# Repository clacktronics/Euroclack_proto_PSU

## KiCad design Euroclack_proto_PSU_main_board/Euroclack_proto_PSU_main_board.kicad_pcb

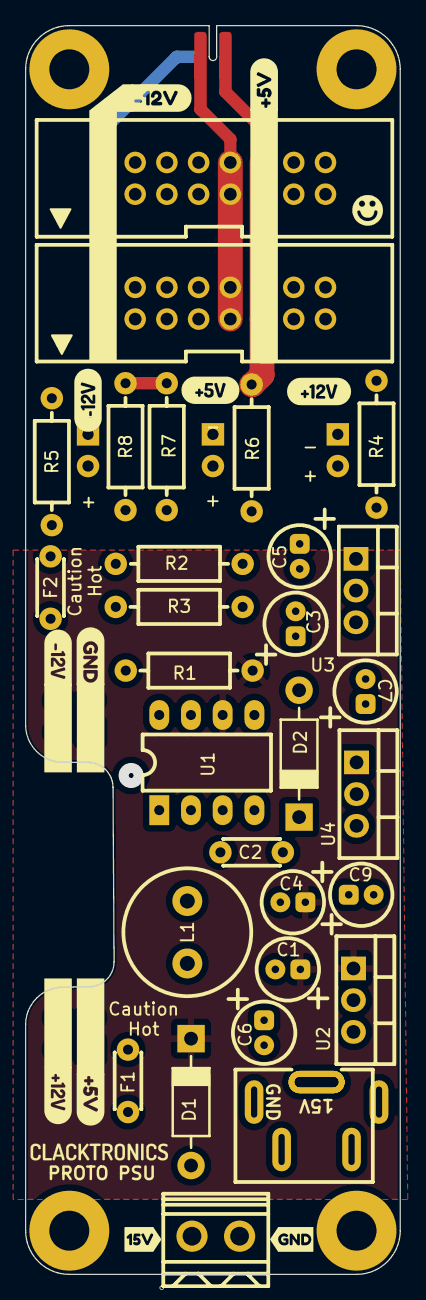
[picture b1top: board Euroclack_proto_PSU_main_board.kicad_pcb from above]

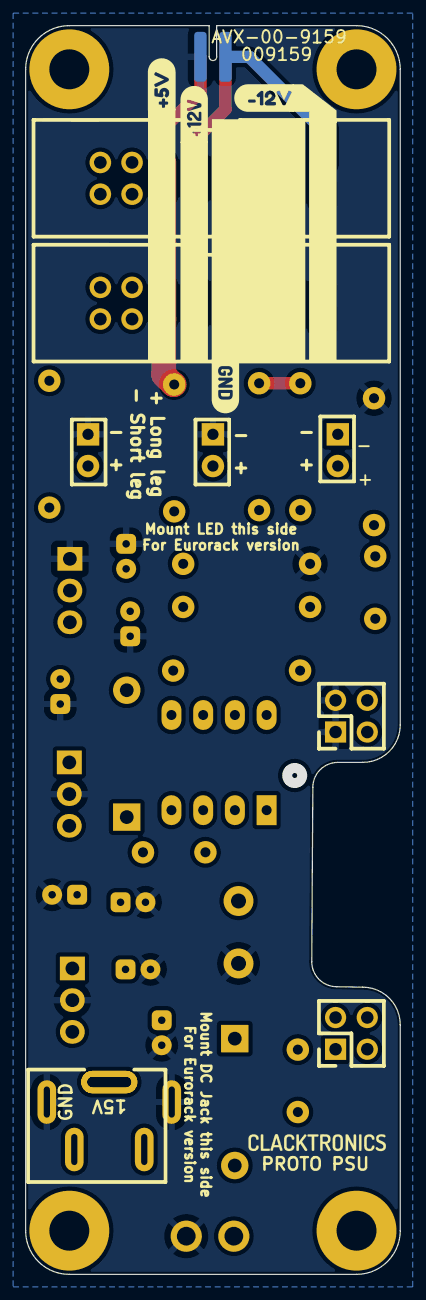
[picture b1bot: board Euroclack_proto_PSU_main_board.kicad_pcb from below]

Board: 4 copper layers, 30.0 x 100.0 mm, 51 parts (7 on the bottom side), 16 nets.

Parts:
C1, C3, C4, C5: 100uF; C_TH_Elec_5mm_P2mm
C2: 220p; C_TH_Disc_P5.00mm
C6, C7, C9: 10uf; C_TH_Elec_5mm_P2mm
D1, D2: 1N5819; D_TH_DO-41_P10.16mm
D3, D4, D5: LED; LED_D3.0mm
F1, F2: JK60-030; C_TH_Disc_P5.00mm
J1, J4: Jack-DC; DC-012A-20A
J2, J3: Conn_02x08_Odd_Even; Eurorack_16_header
J5: Screw_Terminal_01x02; CONN-TH_2P-P3.81_DB125-3.81-2P-BK-S
J6, J7: Conn_02x02_Odd_Even; PinHeader_2x02_P2.54mm_Vertical
J8: AVX-00-9159; AVX-00-9159-004
L1: 220uH; L_Radial_D10.0mm_P5.00mm_Neosid_SD12_style3
R1: 0R220; R_TH_Axial_250mw_P10.16mm_Horizontal
R2, R4, R5, R6, R7, R8: 11k; R_TH_Axial_250mw_P10.16mm_Horizontal
R3: 1k; R_TH_Axial_250mw_P10.16mm_Horizontal
U1: MC34063AD; DIP-8_W7.62mm_LongPads
U2: L7812; TO-220-3_Vertical
U3: L7912; TO-220-3_Vertical
U4: L7805; TO-220-3_Vertical
kibuzzard-63C133C2: G***; kibuzzard-63C133C2
kibuzzard-63C133DA: G***; kibuzzard-63C133DA
kibuzzard-63C1342B: G***; kibuzzard-63C1342B
kibuzzard-63C1369E: G***; kibuzzard-63C1369E
kibuzzard-63C6800E: G***; kibuzzard-63C6800E
kibuzzard-63C13629: G***; kibuzzard-63C13629
kibuzzard-63C68039: G***; kibuzzard-63C68039
kibuzzard-6399A8B6: G***; kibuzzard-6399A8B6
kibuzzard-6399A8D9: G***; kibuzzard-6399A8D9
kibuzzard-6399A96E: G***; kibuzzard-6399A96E
kibuzzard-6399A927, kibuzzard-6399A927#2, kibuzzard-6399A927#3: G***; kibuzzard-6399A927
kibuzzard-6399AAFB: G***; kibuzzard-6399AAFB
kibuzzard-6399ABE2: G***; kibuzzard-6399ABE2

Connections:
+5V: C9.1, J2.11, J2.12, J3.11, J3.12, J7.1, J7.2, J8.2, R6.2, R7.2, R8.2, U4.3 (OUT)
+12V: F1.2, J2.9, J2.10, J3.9, J3.10, J7.3, J7.4, J8.1, R4.2, U4.1 (IN)
-12V: D4.1 (K), F2.2, J2.1, J2.2, J3.1, J3.2, J6.3, J6.4, J8.3
GND: C1.2, C3.1, C4.2, C5.1, C6.2, C7.1, C9.2, D3.1 (K), D5.1 (K), J1.2, J2.3, J2.4, J2.5, J2.6, J2.7, J2.8, J3.3, J3.4, J3.5, J3.6, J3.7, J3.8, J4.2, J5.2, J6.1, J6.2, J8.4, L1.2, R2.1, R5.2, U2.2 (GND), U3.1 (GND), U4.2 (GND)
unnamed: D1.2 (A), J1.1, J4.1, J5.1
unnamed: C2.2, C3.2, C5.2, D2.2 (A), R3.1, U1.4 (GND), U3.2 (VI)
unnamed: D2.1 (K), L1.1, U1.2 (SwE)
unnamed: D3.2 (A), R4.1
unnamed: D4.2 (A), R5.1
unnamed: D5.2 (A), R6.1, R7.1, R8.1
unnamed: R1.2, U1.1 (SwC), U1.7 (Ipk), U1.8 (DC)
unnamed: C2.1, U1.3 (TC)
unnamed: R2.2, R3.2, U1.5 (Vfb)
unnamed: C6.1, F1.1, U2.3 (OUT)
unnamed: C7.2, F2.1, U3.3 (VO)
VCC: C1.1, C4.1, D1.1 (K), R1.1, U1.6 (Vin), U2.1 (IN)

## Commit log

2023-06-01 new files
